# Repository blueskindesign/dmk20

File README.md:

# dmk20
dmk20 is a 17 or 20 key DIY mechanical keyboard. The 100% through-hole kit can be paired with your choice of Cherry MX style switches and keycaps for a numpad, macropad or even half of a 4×10 split ortholinear.

See docs/ for assembly instructions.

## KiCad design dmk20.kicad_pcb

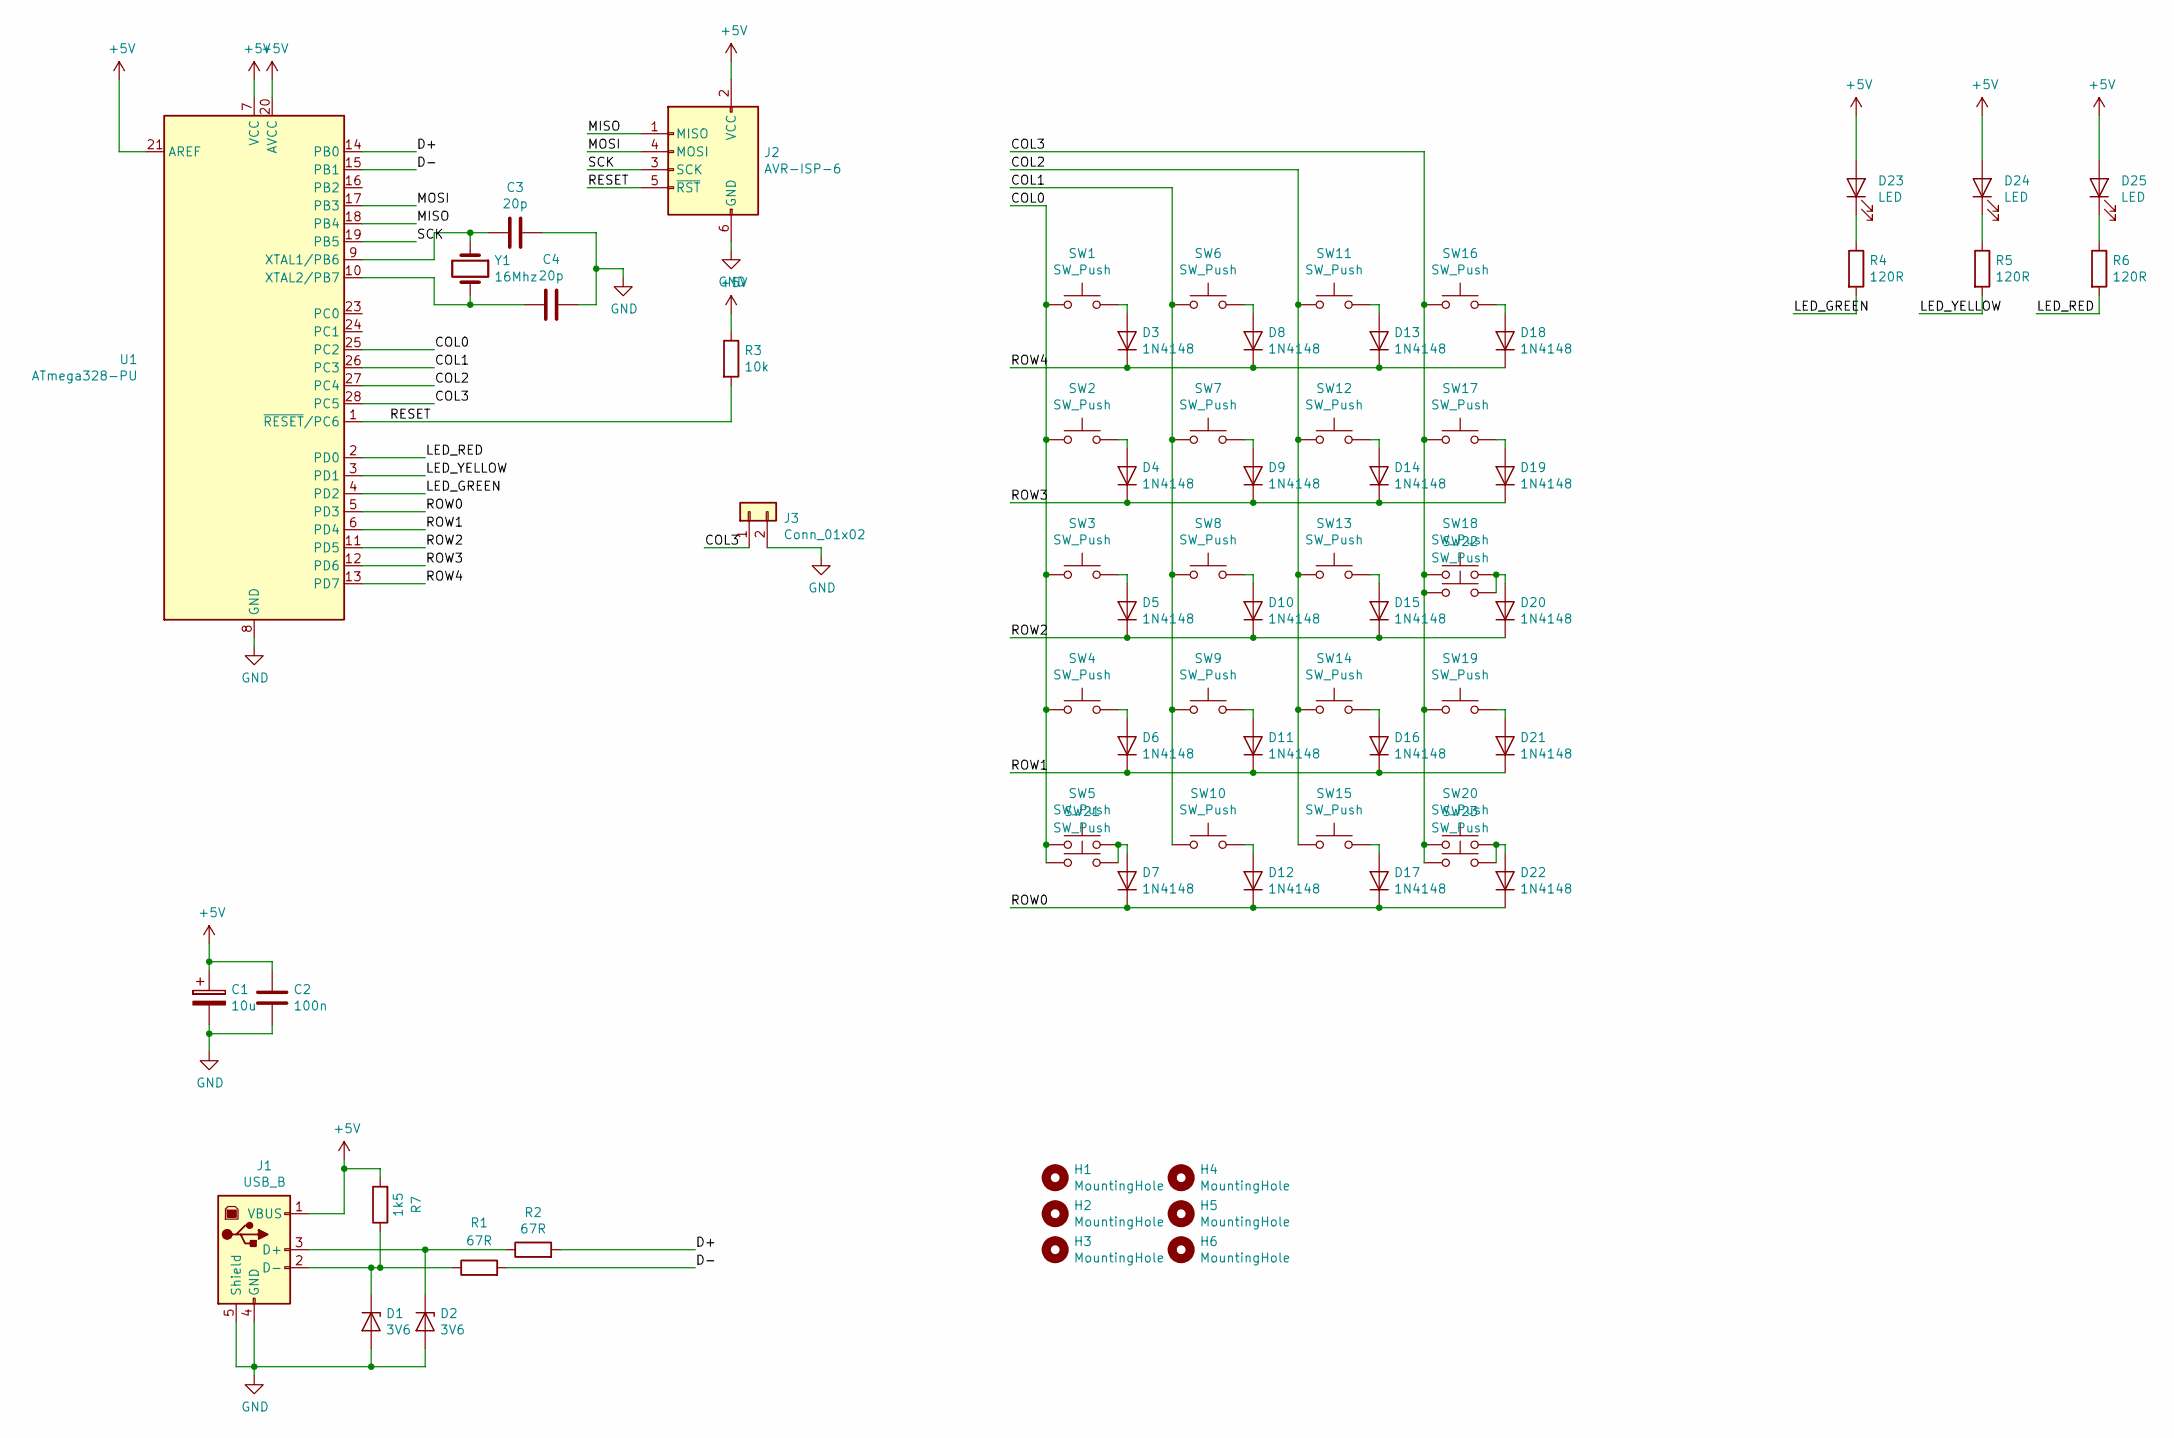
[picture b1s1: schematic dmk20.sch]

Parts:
C1: 10u; CP_Radial_D5.0mm_P2.00mm
C2: 100n; C_Disc_D4.3mm_W1.9mm_P5.00mm
C3, C4: 20p; C_Disc_D3.0mm_W1.6mm_P2.50mm
D1, D2: 3V6; D_T-1_P5.08mm_Horizontal
D3, D4, D5, D6, D7, D8, D9, D10, D11, D12, D13, D14, D15, D16, D17, D18, D19, D20, D21, D22: 1N4148; D_T-1_P5.08mm_Horizontal
D23, D24, D25: LED; LED_D3.0mm_Clear
H1, H2, H3, H4, H5, H6: MountingHole; MountingHole_2.2mm_M2_Pad
J1: USB_B; USB_B_OST_USB-B1HSxx_Horizontal
J2: AVR-ISP-6; PinHeader_2x03_P2.54mm_Vertical
J3: Conn_01x02; PinHeader_1x02_P2.54mm_Vertical
R1, R2: 67R; R_Axial_DIN0204_L3.6mm_D1.6mm_P5.08mm_Horizontal
R3: 10k; R_Axial_DIN0204_L3.6mm_D1.6mm_P5.08mm_Horizontal
R4, R5, R6: 120R; R_Axial_DIN0204_L3.6mm_D1.6mm_P5.08mm_Horizontal
R7: 1k5; R_Axial_DIN0204_L3.6mm_D1.6mm_P5.08mm_Horizontal
SW1, SW2, SW3, SW4, SW5, SW6, SW7, SW8, SW9, SW10, SW11, SW12, SW13, SW14, SW15, SW16, SW17, SW18, SW19, SW20: SW_Push; SW_Cherry_MX1A_1.00u_PCB
SW21: SW_Push; SW_Cherry_MX1A_2.00u_PCB
SW22, SW23: SW_Push; SW_Cherry_MX1A_2.00u_Vertical_PCB
U1: ATmega328-PU; DIP-28_W7.62mm
Y1: 16Mhz; Crystal_HC49-4H_Vertical

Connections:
+5V: C1.1, C2.1, D23.2 (A), D24.2 (A), D25.2 (A), J1.1 (VBUS), J2.2 (VCC), R3.1, R7.2, U1.7 (VCC), U1.20 (AVCC), U1.21 (AREF)
/COL0: SW1.1, SW2.1, SW3.1, SW4.1, SW5.1, SW21.1, U1.25 (PC2)
/COL1: SW6.1, SW7.1, SW8.1, SW9.1, SW10.1, U1.26 (PC3)
/COL2: SW11.1, SW12.1, SW13.1, SW14.1, SW15.1, U1.27 (PC4)
/COL3: J3.1, SW16.1, SW17.1, SW18.1, SW19.1, SW20.1, SW22.1, SW23.1, U1.28 (PC5)
/D+: R2.2, U1.14 (PB0)
/D-: R1.2, U1.15 (PB1)
/LED_GREEN: R4.2, U1.4 (PD2)
/LED_RED: R6.2, U1.2 (PD0)
/LED_YELLOW: R5.2, U1.3 (PD1)
/MISO: J2.1 (MISO), U1.18 (PB4)
/MOSI: J2.4 (MOSI), U1.17 (PB3)
/RESET: J2.5 (~RST), R3.2, U1.1 (~RESET~/PC6)
/ROW0: D7.1 (K), D12.1 (K), D17.1 (K), D22.1 (K), U1.5 (PD3)
/ROW1: D6.1 (K), D11.1 (K), D16.1 (K), D21.1 (K), U1.6 (PD4)
/ROW2: D5.1 (K), D10.1 (K), D15.1 (K), D20.1 (K), U1.11 (PD5)
/ROW3: D4.1 (K), D9.1 (K), D14.1 (K), D19.1 (K), U1.12 (PD6)
/ROW4: D3.1 (K), D8.1 (K), D13.1 (K), D18.1 (K), U1.13 (PD7)
/SCK: J2.3 (SCK), U1.19 (PB5)
GND: C1.2, C2.2, C3.1, C4.1, D1.2 (A), D2.2 (A), J1.4 (GND), J1.5 (Shield), J2.6 (GND), J3.2, U1.8 (GND), U1.22 (GND)
unnamed: C3.2, U1.9 (XTAL1/PB6), Y1.1
unnamed: C4.2, U1.10 (XTAL2/PB7), Y1.2
unnamed: D1.1 (K), J1.2 (D-), R1.1, R7.1
unnamed: D2.1 (K), J1.3 (D+), R2.1
unnamed: D3.2 (A), SW1.2
unnamed: D4.2 (A), SW2.2
unnamed: D5.2 (A), SW3.2
unnamed: D6.2 (A), SW4.2
unnamed: D7.2 (A), SW5.2, SW21.2
unnamed: D8.2 (A), SW6.2
unnamed: D9.2 (A), SW7.2
unnamed: D10.2 (A), SW8.2
unnamed: D11.2 (A), SW9.2
unnamed: D12.2 (A), SW10.2
unnamed: D13.2 (A), SW11.2
unnamed: D14.2 (A), SW12.2
unnamed: D15.2 (A), SW13.2
unnamed: D16.2 (A), SW14.2
unnamed: D17.2 (A), SW15.2
unnamed: D18.2 (A), SW16.2
unnamed: D19.2 (A), SW17.2
unnamed: D20.2 (A), SW18.2, SW22.2
unnamed: D21.2 (A), SW19.2
unnamed: D22.2 (A), SW20.2, SW23.2
unnamed: D23.1 (K), R4.1
unnamed: D24.1 (K), R5.1
unnamed: D25.1 (K), R6.1

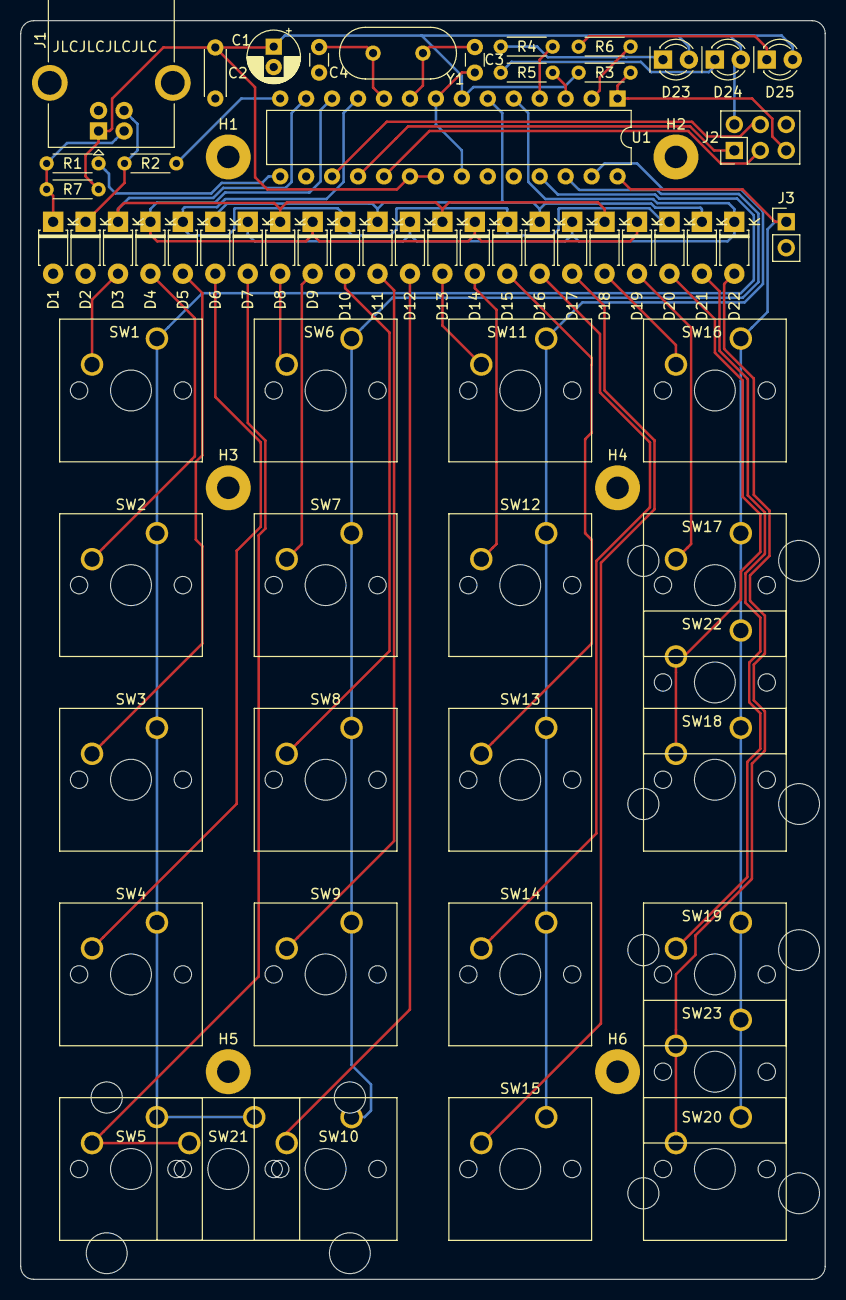
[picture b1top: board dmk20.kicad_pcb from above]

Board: 2 copper layers, 78.7 x 123.2 mm, 70 parts (0 on the bottom side), 47 nets.

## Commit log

2020-01-02 Initial commit.
2020-01-07 added assembly instructions

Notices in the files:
dmk20.kicad_pcb:
(C) 2019 Blueskin Design Ltd
